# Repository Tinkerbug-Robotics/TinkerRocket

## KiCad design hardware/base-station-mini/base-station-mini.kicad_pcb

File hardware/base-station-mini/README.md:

# base-station-mini

A reduced-feature ground station. **"Mini" means fewer features, not a smaller
board** — the outline is still base-station's 30.27 × 90.50 mm. Nothing here is
trying to shrink; it is trying to do less.

Currently rev **V1**, never fabricated.

## What it drops, and what it gains

Against [`base-station/`](../base-station/):

- **The LoRa radio is on-board.** `U16`, an E220-900MM22S on SPI, replaces the
  UART header that fed an external [`lora-daughterboard/`](../lora-daughterboard/).
  That removes the daughterboard, its connector, and the 5 V `V_LORA` boost that
  supplied it — the module runs straight off +3V3.
- **No external charger sheet.** Dropped from the root, along with the
  `PosADC`/`MidADC` sense lines it fed. `external_charger.kicad_sch` was deleted
  outright on 2026-08-12 rather than left orphaned on disk.
- **No sensor I²C.** `SDA_SENS`/`SCL_SENS` are gone, which is what freed GPIO33
  and GPIO34 for the radio.
- **`+3V3` comes from a fixed-output TPS63021** buck-boost rather than the
  adjustable TPS63020 and its feedback divider. base-station moved to the same
  part at V6.

## The battery thermistor is board-mounted, and that is a compromise

`TH1` feeds the BQ21040's `TS` pin, which gates charging on temperature. It is a
10 kΩ-at-25 °C NTC, B25/85 = 3435 K, ±1 % on both, in an 0603 chip package, on
the component side at the far end of the board from the charger. `R53` (210 kΩ,
`TS` to ground) is TI's TTDM-defeat resistor and is unchanged — with the same
resistance-temperature curve the charger's temperature window does not move.

Until 2026-08-27 `TH1` was a two-pin 2.54 mm land for a **leaded** thermistor of
that same curve, meant to be taped to the 18650 so `TS` read *cell* temperature.
The cell holder leaves no room for a part under the cell, so the sensor moved
onto the board.

**What that costs.** The NTC now reads the ground plane, not the cell, and its
self-heat bias runs one way: a warm board makes the charger believe the pack is
warmer than it is.

- On the hot side that is conservative — charging is inhibited early.
- On the **cold** side it is not. Board self-heat can mask a genuinely cold cell
  and allow a sub-0 °C charge, which is the failure the `TS` pin exists to
  prevent.

Placement mitigates this; it does not remove it. `TH1` sits 25 mm from the
charger — the dominant heat source while charging, dissipating on the order of
1 W as a linear regulator at the ~0.79 A `R52` programs — 27 mm from the
buck-boost and 15 mm from the ESP32-S3. Weighted by dissipation over distance
that is about 37 % less coupling than the old land, which sat 8.6 mm from the
buck-boost and 13.5 mm from the charger. A solid inner ground plane keeps the
board close to isothermal, so what remains is a board-wide offset rather than a
local hot spot.

Everywhere on the board that is further from the heat needs a sensor trace
threaded through the ESP32-S3 fanout or the chip antenna's ground-via fence;
neither is worth it for a few degrees. The route as built is 19 mm on `F.Cu`
with no vias.

**Open at first article:** with the board charging, compare the `TS` node
against a reference probe on the cell at room temperature and near 0 °C, and
confirm the offset is small enough to accept. If it is not, the fix is a wired
probe on a connector, not a different chip.

## The radio pinout is deliberately identical to lora-daughterboard

All eight ESP32↔E220 signals land on the same GPIOs as the fabbed
`lora-daughterboard`, so the `radio_board` firmware pin map applies unchanged:

| net | E220 | GPIO |
|---|---|---|
| `L_SCK` | 15 SCK | 17 |
| `L_CS` | 14 NSS | 18 |
| `L_MOSI` | 13 MOSI | 21 |
| `L_MISO` | 12 MISO | 33 |
| `L_BUSY` | 11 BUSY | 34 |
| `L_RXEN` | 10 RXEN | 35 |
| `L_RST` | 3 NRST | 38 |
| `L_DI01` | 20 DIO1 | 2 |

`L_DI02` is a module-local loop from DIO2 to TXEN, so the SX1262 drives its own
RF switch and costs no GPIO. DIO3 is unconnected. Both match the daughterboard.

## Provenance

The design started as a copy of `base-station` and diverges from there. There is
**no ongoing relationship** between them — nothing is shared, nothing tracks
upstream, and a change to one is not expected to reach the other. Treat anything
still inherited as a first draft to be justified on its own terms.

Two things were deliberately left behind at the fork:

- **`base-station`'s design reviews** (`prefab-review-2026-08-02.md`,
  `power-switch-review-2026-08-02.md`) — records of a review of *that* board.
  Copying them here would assert this board has been reviewed when it has not.
  They remain the best reading on the inherited power architecture; read them
  there.
- **`outputs.kicad_sch`**, an empty sheet in `base-station/` referenced by
  nothing. See the leftovers note in [`../README.md`](../README.md).

## Status

Not fabbed, no tag, no firmware project of its own. Schematic and PCB are in
sync and fully routed — 0 parity issues, 0 unconnected.

Reviewed 2026-08-12: [`prefab-review-2026-08-12.md`](prefab-review-2026-08-12.md).
Four items to close before fab, none of them blockers; the review's *Before fab*
section is the checklist. See also *Sending a board to fab* in
[`../README.md`](../README.md).

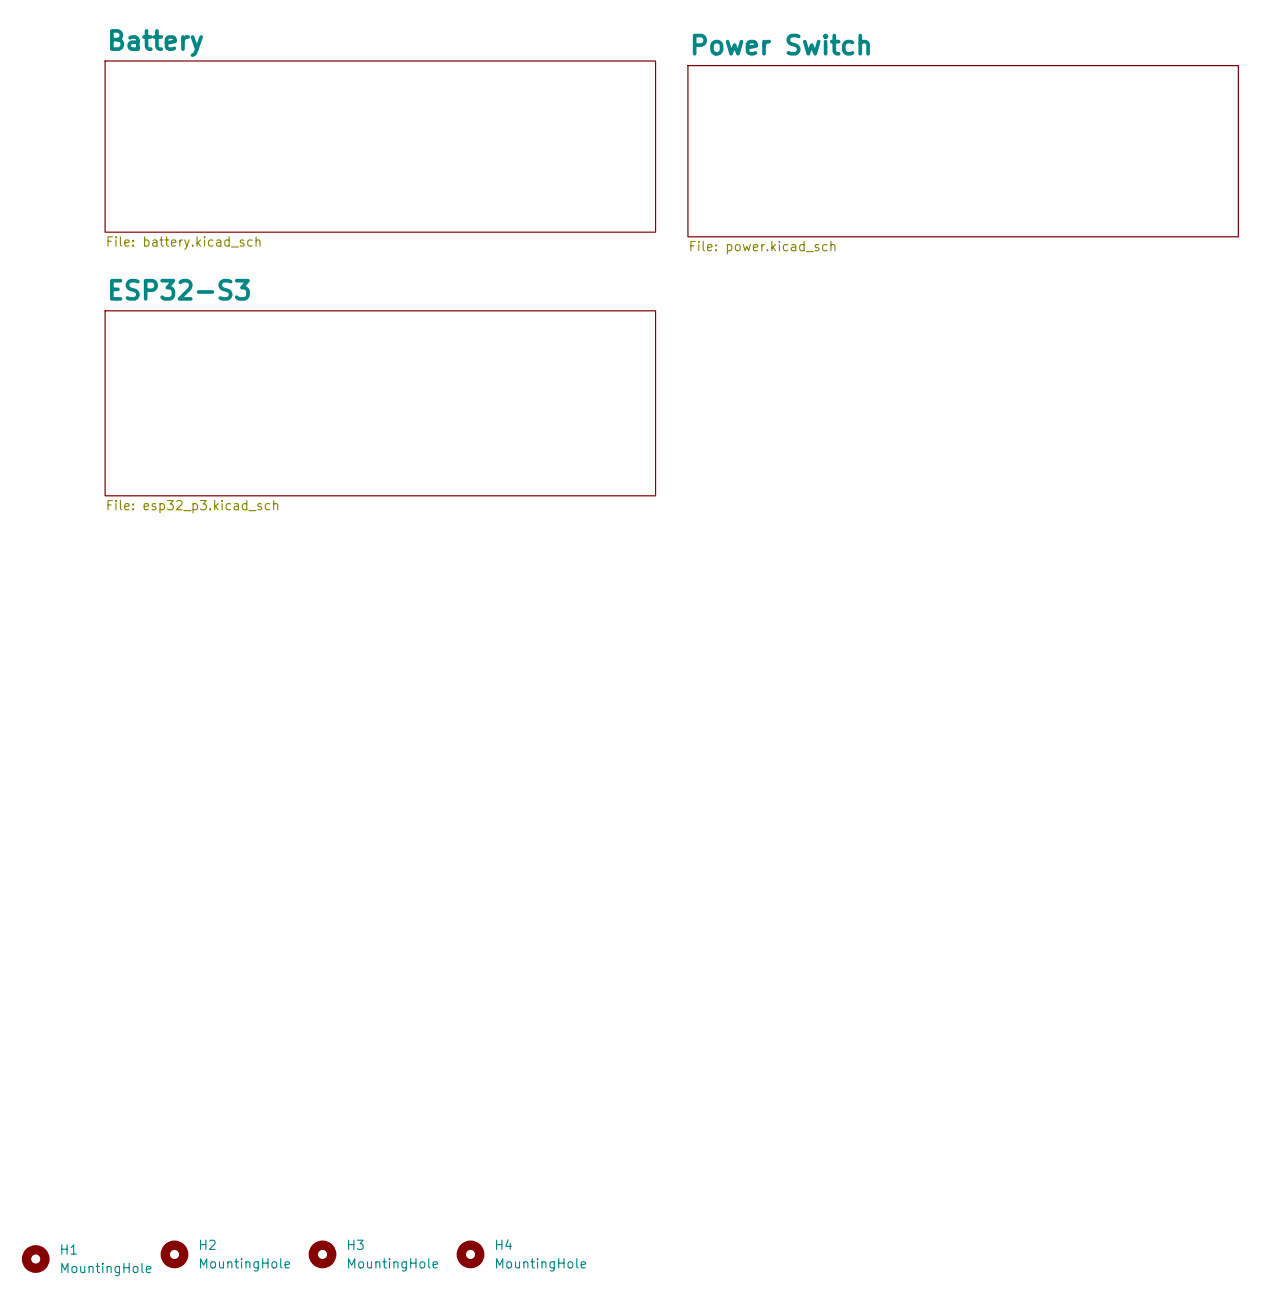
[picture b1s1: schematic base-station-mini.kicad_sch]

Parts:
H1, H2, H3, H4: MountingHole; MountingHole_2.2mm_M2_DIN965_Pad

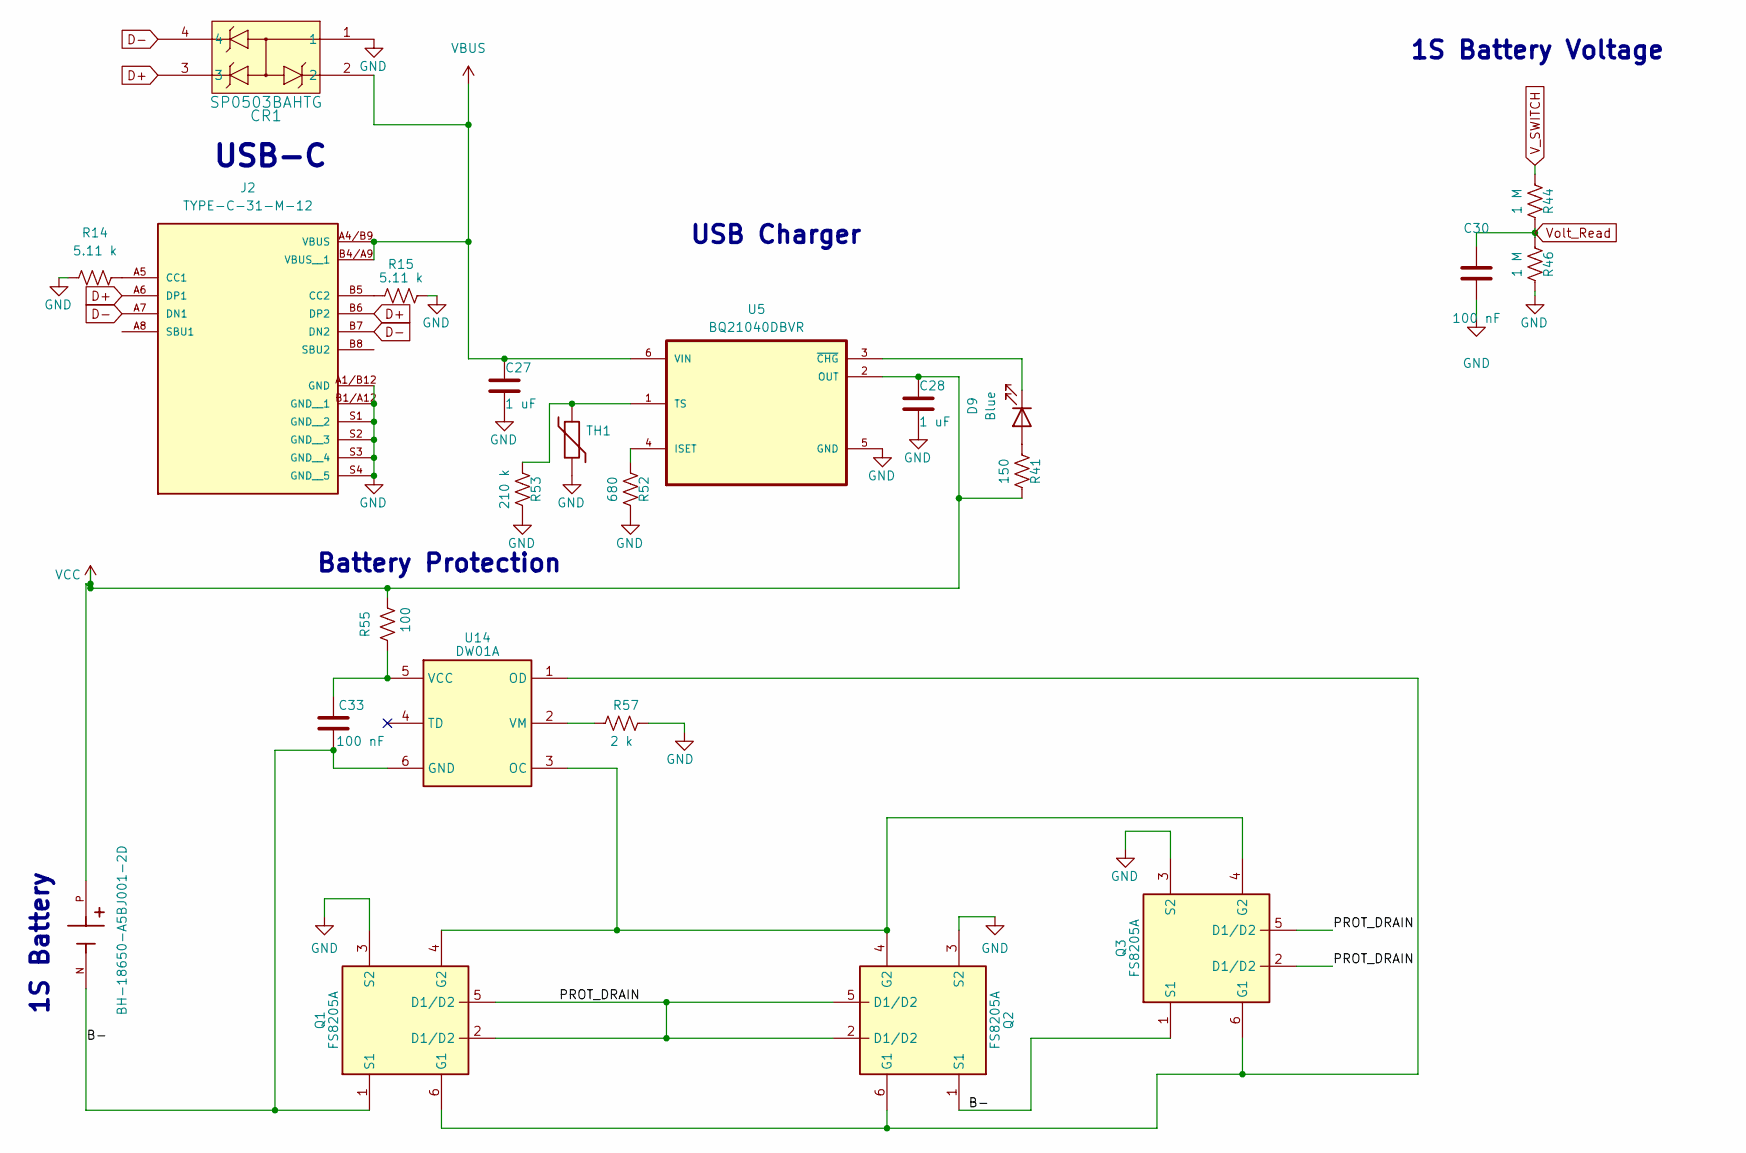
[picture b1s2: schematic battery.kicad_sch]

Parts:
BT2: BH-18650-A5BJ001-2D; BAT_BH-18650-A5BJ001-2D; PARTREV D; LCSC_Part_Number C19184083
C27, C28: 1 uF; C_0402_1005Metric; MPN CL05A105KO5NNNC
C30, C33: 100 nF; C_0402_1005Metric; MPN CL05B104KO5NNNC
CR1: SP0503BAHTG; TVS-SP05_LTF; MPN SP0503BAHTG
D9: Blue; LED_D3.0mm; MPN XL-304UBC
J2: TYPE-C-31-M-12; USB_C_HRO_TYPE-C-31-M-12; MPN TYPE-C-31-M-12
Q1, Q2, Q3: FS8205A; SOT-23-6; MPN FS8205A; LCSC_Part_Number C2830320
R14, R15: 5.11 k; R_0402_1005Metric; MPN RC0402FR-075K11L
R41: 150; R_0402_1005Metric; MPN RC0402FR-07150RL
R44, R46: 1 M; R_0402_1005Metric; MPN RC0402FR-071ML
R52: 680; R_0402_1005Metric; MPN RC0402FR-07680RL
R53: 210 k; R_0402_1005Metric; MPN RC0402FR-07210KL
R55: 100; R_0402_1005Metric; MPN RC0402FR-07100RL
R57: 2 k; R_0402_1005Metric; MPN RC0402FR-072KL
TH1: Thermistor 10k NTC B3435; R_0603_1608Metric; MPN TX06F103F3435ER
U5: BQ21040DBVR; SOT95P280X145-6N; MPN BQ21040DBVR; DigiKey_Part_Number 296-47315-1-ND
U14: DW01A; SOT-23-6; MPN DW01A; LCSC_Part_Number C351410

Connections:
/Battery/B-: BT2.N, C33.2, Q1.1 (S1), Q2.1 (S1), Q3.1 (S1), U14.6 (GND)
/Battery/PROT_DRAIN: Q1.2 (D1/D2), Q1.5 (D1/D2), Q2.2 (D1/D2), Q2.5 (D1/D2), Q3.2 (D1/D2), Q3.5 (D1/D2)
D+: CR1.3, J2.A6 (DP1), J2.B6 (DP2); also elsewhere on the board
D-: CR1.4, J2.A7 (DN1), J2.B7 (DN2); also elsewhere on the board
GND: C27.2, C28.2, C30.2, CR1.1, J2.A1/B12 (GND), J2.B1/A12 (GND__1), J2.S1 (GND__2), J2.S2 (GND__3), J2.S3 (GND__4), J2.S4 (GND__5), Q1.3 (S2), Q2.3 (S2), Q3.3 (S2), R14.1, R15.2, R46.2, R52.2, R53.2, R57.2, TH1.2, U5.5 (GND); also elsewhere on the board
unnamed: D9.2 (A), R41.1
unnamed: D9.1 (K), U5.3 (~CHG)
unnamed: J2.A5 (CC1), R14.2
unnamed: J2.B5 (CC2), R15.1
unnamed: Q1.6 (G1), Q2.6 (G1), Q3.6 (G1), U14.1 (OD)
unnamed: Q1.4 (G2), Q2.4 (G2), Q3.4 (G2), U14.3 (OC)
unnamed: R52.1, U5.4 (ISET)
unnamed: R53.1, TH1.1, U5.1 (TS)
unnamed: C33.1, R55.2, U14.5 (VCC)
unnamed: R57.1, U14.2 (VM)
VBUS: C27.1, CR1.2, J2.A4/B9 (VBUS), J2.B4/A9 (VBUS__1), U5.6 (VIN)
VCC: BT2.P, C28.1, R41.2, R55.1, U5.2 (OUT); also elsewhere on the board
V_SWITCH: R44.1; also elsewhere on the board
Volt_Read: C30.1, R44.2, R46.1; also elsewhere on the board

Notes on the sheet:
1S Battery
1S Battery Voltage
Battery Protection
USB-C
USB Charger

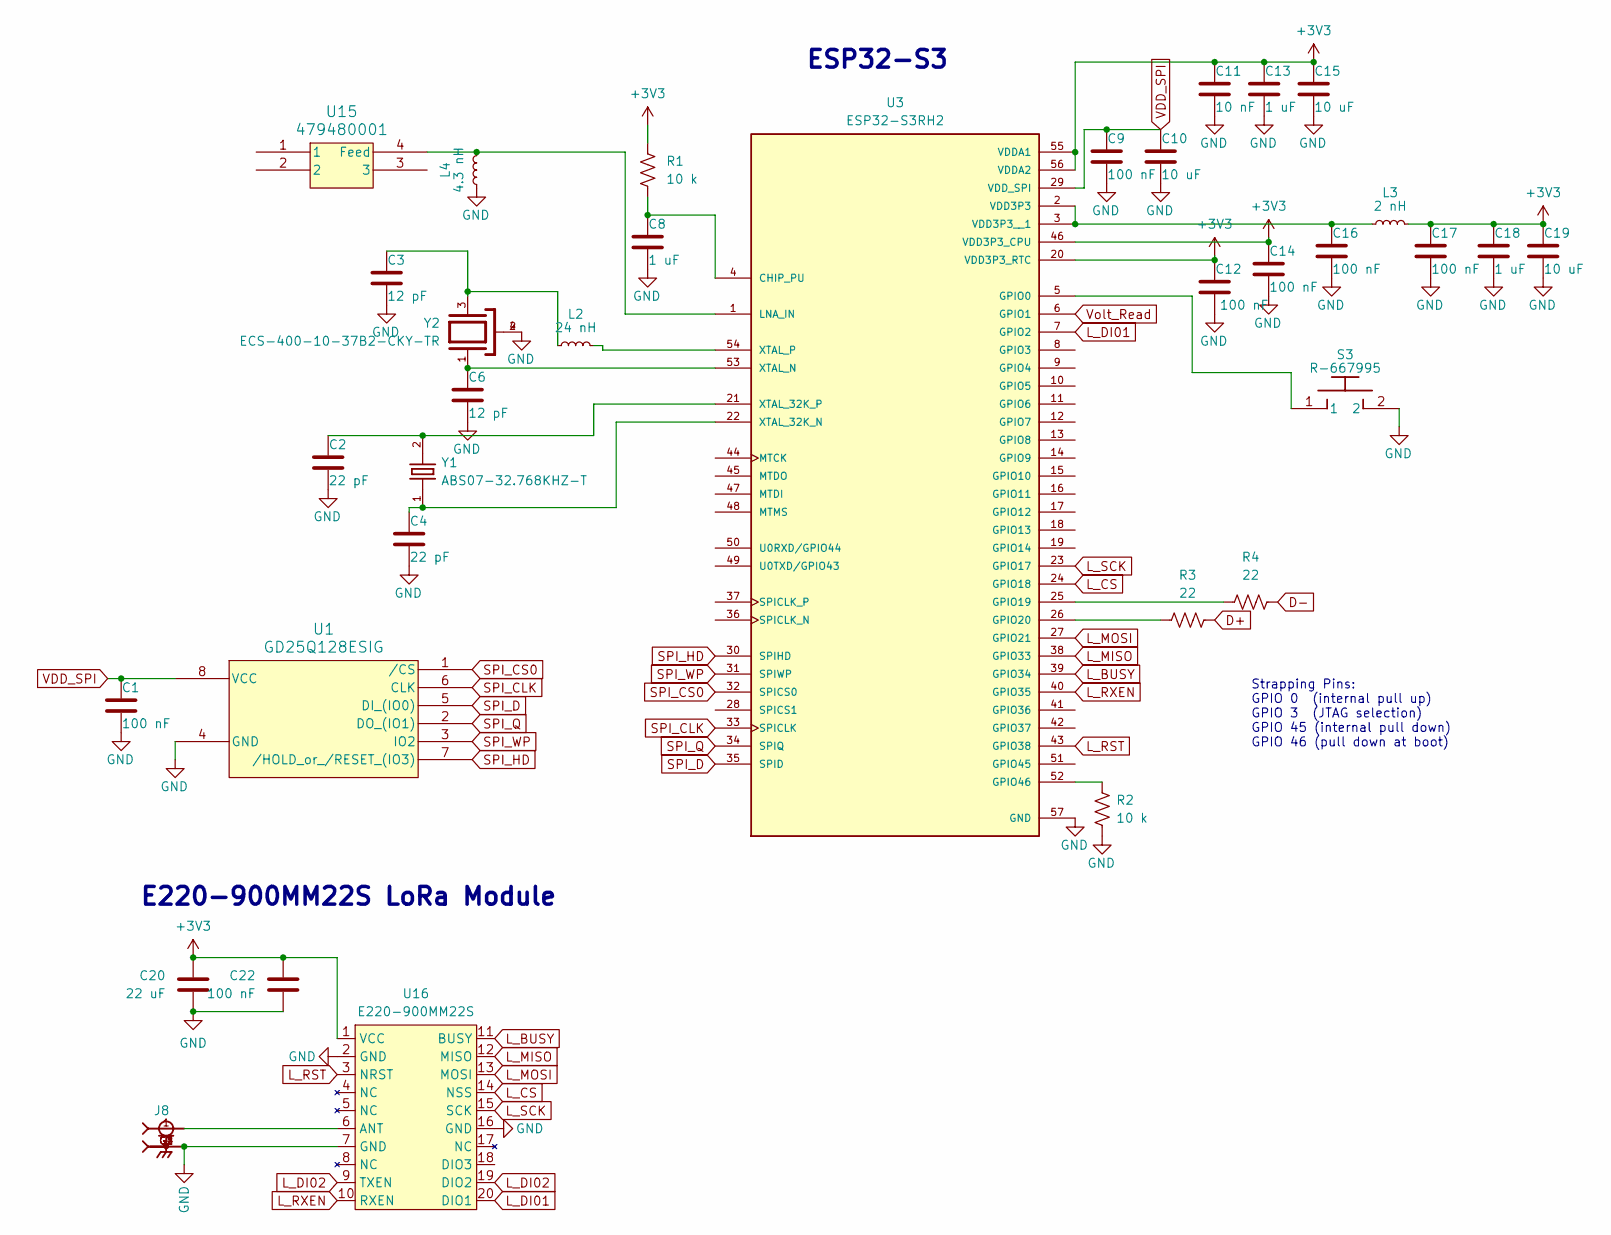
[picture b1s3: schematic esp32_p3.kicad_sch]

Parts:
C1, C9, C12, C14, C16, C17, C22: 100 nF; C_0402_1005Metric; MPN CL05B104KO5NNNC
C2, C4: 22 pF; C_0402_1005Metric; MPN CL05C220JB5NNNC
C3, C6: 12 pF; C_0402_1005Metric; MPN CL05C120JB5NNNC
C8, C13, C18: 1 uF; C_0402_1005Metric; MPN CL05A105KO5NNNC
C10, C15, C19: 10 uF; C_0402_1005Metric; MPN CL05A106MQ5NUNC
C11: 10 nF; C_0402_1005Metric; MPN CL05B103KB5NNNC
C20: 22 uF; C_0805_2012Metric; MPN CL21A226MOQNNNE
J8: CON-SMA-EDGE-S; RFSOLUTIONS_CON-SMA-EDGE-S; PARTREV 1
L2: 24 nH; L_0402_1005Metric; MPN LQW15AN24NH00D
L3: 2 nH; L_0402_1005Metric; MPN LQG15HS2N0S02D
L4: 4.3 nH; L_0402_1005Metric; MPN LQW15AN4N3C00D
R1, R2: 10 k; R_0402_1005Metric; MPN RC0402FR-0710KL
R3, R4: 22; R_0402_1005Metric; MPN RC0402FR-0722RL
S3: R-667995; R-667995_MIT; MPN R-667995
U1: GD25Q128ESIG; SOIC127P790X216-8N; MPN GD25Q128ESIG
U3: ESP32-S3RH2; IC_ESP32-S3; PARTREV v1.2
U15: 479480001; ANT_47948-0001_MOL; MPN 479480001
U16: E220-900MM22S; MPN E220-900MM22S
Y1: ABS07-32.768KHZ-T; XTAL_SC-32S_3215; MPN ABS07-32.768KHZ-T
Y2: ECS-400-10-37B2-CKY-TR; XTAL_ECS-400-10-37B2-CKY-TR; PARTREV 2021

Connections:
+3V3: C11.1, C12.1, C13.1, C14.1, C15.1, C17.1, C18.1, C19.1, C20.2, C22.2, L3.2, R1.1, U3.20 (VDD3P3_RTC), U3.46 (VDD3P3_CPU), U3.55 (VDDA1), U3.56 (VDDA2), U16.1 (VCC); also elsewhere on the board
D+: R3.1; also elsewhere on the board
D-: R4.1; also elsewhere on the board
GND: C1.2, C2.2, C3.2, C4.2, C6.2, C8.2, C9.2, C10.2, C11.2, C12.2, C13.2, C14.2, C15.2, C16.2, C17.2, C18.2, C19.2, C20.1, C22.1, J8.G1, J8.G2, J8.G3, J8.G4, L4.1, R2.2, S3.2, U1.4 (GND), U3.57 (GND), U16.2 (GND), U16.7 (GND), U16.16 (GND), Y2.2, Y2.4; also elsewhere on the board
L_BUSY: U3.39 (GPIO34), U16.11 (BUSY)
L_CS: U3.24 (GPIO18), U16.14 (NSS)
L_DI01: U3.7 (GPIO2), U16.20 (DIO1)
L_DI02: U16.9 (TXEN), U16.19 (DIO2)
L_MISO: U3.38 (GPIO33), U16.12 (MISO)
L_MOSI: U3.27 (GPIO21), U16.13 (MOSI)
L_RST: U3.43 (GPIO38), U16.3 (NRST)
L_RXEN: U3.40 (GPIO35), U16.10 (RXEN)
L_SCK: U3.23 (GPIO17), U16.15 (SCK)
unnamed: C3.1, L2.1, Y2.3
unnamed: C8.1, R1.2, U3.4 (CHIP_PU)
unnamed: S3.1, U3.5 (GPIO0)
unnamed: R4.2, U3.25 (GPIO19)
unnamed: R3.2, U3.26 (GPIO20)
unnamed: R2.1, U3.52 (GPIO46)
unnamed: C16.1, L3.1, U3.2 (VDD3P3), U3.3 (VDD3P3__1)
unnamed: C4.1, U3.22 (XTAL_32K_N), Y1.1
unnamed: C2.1, U3.21 (XTAL_32K_P), Y1.2
unnamed: C6.1, U3.53 (XTAL_N), Y2.1
unnamed: L2.2, U3.54 (XTAL_P)
unnamed: L4.2, U3.1 (LNA_IN), U15.4 (Feed_4)
unnamed: J8.1, U16.6 (ANT)
SPI_CLK: U1.6 (CLK), U3.33 (SPICLK)
SPI_CS0: U1.1 (/CS), U3.32 (SPICS0)
SPI_D: U1.5 (DI_(IO0)), U3.35 (SPID)
SPI_HD: U1.7 (/HOLD_or_/RESET_(IO3)), U3.30 (SPIHD)
SPI_Q: U1.2 (DO_(IO1)), U3.34 (SPIQ)
SPI_WP: U1.3 (IO2), U3.31 (SPIWP)
VDD_SPI: C1.1, C9.1, C10.1, U1.8 (VCC), U3.29 (VDD_SPI)
Volt_Read: U3.6 (GPIO1); also elsewhere on the board

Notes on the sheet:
Strapping Pins: GPIO 0 (internal pull up) GPIO 3 (JTAG selection) GPIO 45 (internal pull down) GPIO 46 (pull down at boot)
ESP32-S3
E220-900MM22S LoRa Module

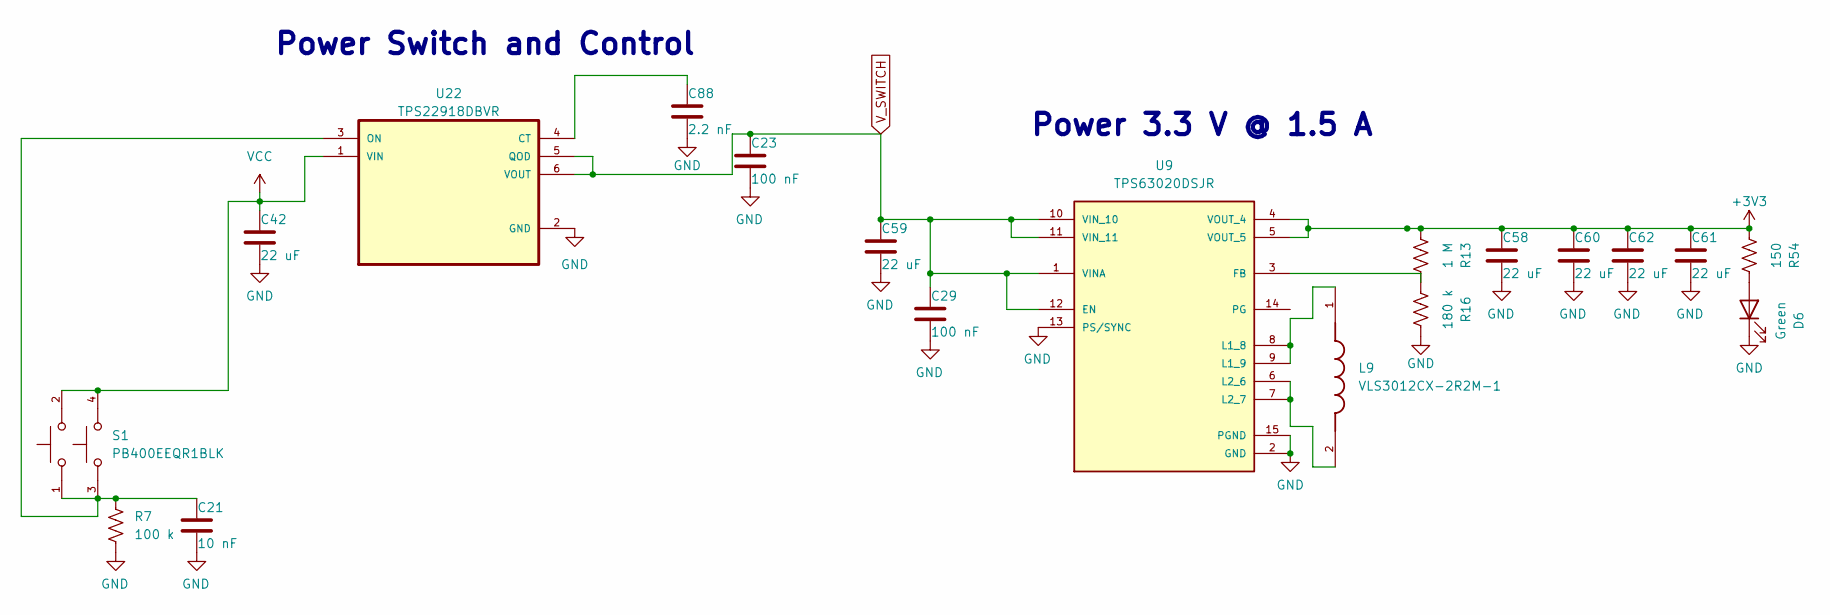
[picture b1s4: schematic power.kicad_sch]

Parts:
C21: 10 nF; C_0402_1005Metric; MPN CL05B103KB5NNNC
C23, C29: 100 nF; C_0402_1005Metric; MPN CL05B104KO5NNNC
C42, C58, C59, C60, C61, C62: 22 uF; C_0805_2012Metric; MPN CL21A226MOQNNNE
C88: 2.2 nF; C_0402_1005Metric; MPN CC0402KRX7R9BB222
D6: Green; LED_D3.0mm; MPN XL-302SYGD
L9: VLS3012CX-2R2M-1; IND_VLS3012CX-2R2M-1; PARTREV N/A
R7: 100 k; R_0402_1005Metric; MPN RC0402FR-07100KL
R13: 1 M; R_0402_1005Metric; MPN RC0402FR-071ML
R16: 180 k; R_0402_1005Metric; MPN RC0402FR-07180KL
R54: 150; R_0402_1005Metric; MPN RC0402FR-07150RL
S1: PB400EEQR1BLK; SW_PB400EEQR1BLK; PARTREV A
U9: TPS63020DSJR; IC_TPS63021DSJR; PARTREV I
U22: TPS22918DBVR; SOT95P280X145-6N; MPN TPS22918DBVR

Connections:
+3V3: C58.1, C60.1, C61.1, C62.1, R13.1, R54.1, U9.4 (VOUT_4), U9.5 (VOUT_5); also elsewhere on the board
GND: C21.2, C23.2, C29.2, C42.2, C58.2, C59.2, C60.2, C61.2, C62.2, C88.2, D6.1 (K), R7.1, R16.2, U9.2 (GND), U9.13 (PS/SYNC), U9.15 (PGND), U22.2 (GND); also elsewhere on the board
unnamed: D6.2 (A), R54.2
unnamed: R13.2, R16.1, U9.3 (FB)
unnamed: L9.1, U9.8 (L1_8), U9.9 (L1_9)
unnamed: L9.2, U9.6 (L2_6), U9.7 (L2_7)
unnamed: C88.1, U22.4 (CT)
unnamed: C21.1, R7.2, S1.1, S1.3, U22.3 (ON)
VCC: C42.1, S1.2, S1.4, U22.1 (VIN); also elsewhere on the board
V_SWITCH: C23.1, C29.1, C59.1, U9.1 (VINA), U9.10 (VIN_10), U9.11 (VIN_11), U9.12 (EN), U22.5 (QOD), U22.6 (VOUT); also elsewhere on the board

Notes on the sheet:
Power Switch and Control
Power 3.3 V @ 1.5 A

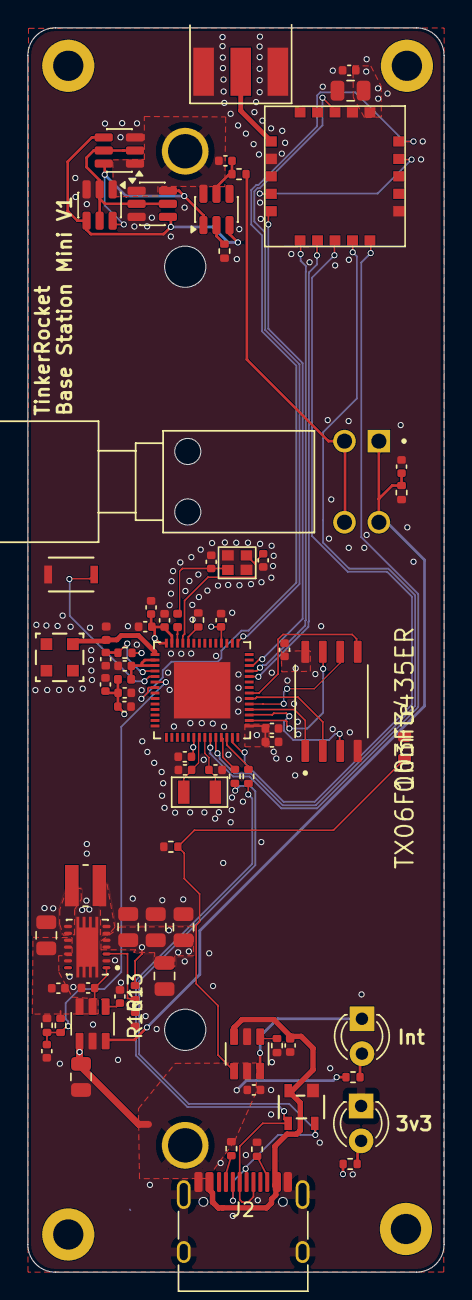
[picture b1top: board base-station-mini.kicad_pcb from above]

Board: 4 copper layers, 30.3 x 90.5 mm, 80 parts (1 on the bottom side), 55 nets.

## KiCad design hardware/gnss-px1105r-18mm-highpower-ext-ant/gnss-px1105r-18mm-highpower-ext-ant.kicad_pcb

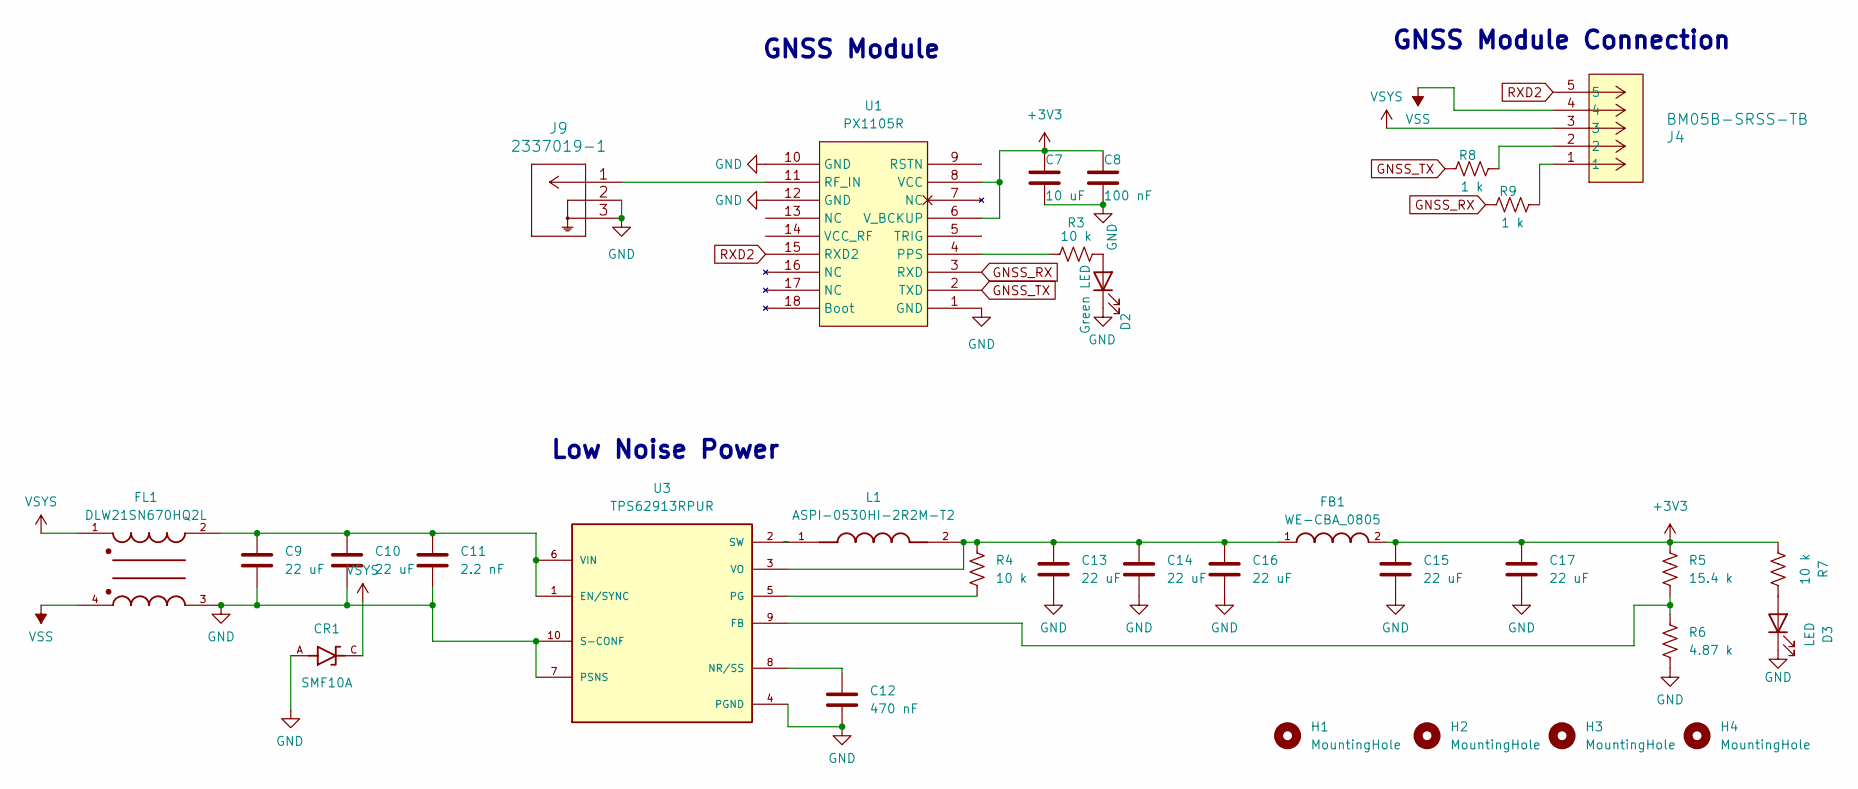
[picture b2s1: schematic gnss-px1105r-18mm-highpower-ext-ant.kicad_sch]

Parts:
C7: 10 uF; C_0805_2012Metric
C8: 100 nF; C_0402_1005Metric
C9, C10, C13, C14, C15, C16, C17: 22 uF; C_0805_2012Metric
C11: 2.2 nF; C_0402_1005Metric
C12: 470 nF; C_0402_1005Metric
CR1: SMF10A; SODFL3617X108N; MPN SMF10A
D2: Green LED; LED_0402_1005Metric
D3: LED; LED_0402_1005Metric
FB1: WE-CBA_0805; WE-CBA_0805_W4.0
FL1: DLW21SN670HQ2L; FIL_DLW21SN670HQ2L
H1, H2, H3, H4: MountingHole; MountingHole_2.2mm_M2_DIN965_Pad
J4: BM05B-SRSS-TB; CONN_BM05B-SRSS-TB_JST
J9: 2337019-1
L1: ASPI-0530HI-2R2M-T2; IND_ASPI-0530HI-2R2M-T2; PARTREV B; DigiKey_Part_Number 535-ASPI-0530HI-2R2M-T2CT-ND
R3, R4, R7: 10 k; R_0402_1005Metric
R5: 15.4 k; R_0402_1005Metric
R6: 4.87 k; R_0402_1005Metric
R8, R9: 1 k; R_0402_1005Metric
U1: PX1105R
U3: TPS62913RPUR; IC_TPS62913RPUR; PARTREV B; DigiKey_Part_Number 296-TPS62913RPURCT-ND

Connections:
+3V3: C7.1, C8.1, C15.1, C17.1, FB1.2, R5.2, R7.1, U1.6 (V_BCKUP), U1.8 (VCC)
GND: C7.2, C8.2, C9.2, C10.2, C11.2, C12.2, C13.2, C14.2, C15.2, C16.2, C17.2, CR1.A, D2.1 (K), D3.1 (K), FL1.3, J9.2, J9.3, R6.1, U1.1 (GND), U1.10 (GND), U1.12 (GND), U3.4 (PGND), U3.7 (PSNS), U3.10 (S-CONF)
GNSS_RX: R9.1, U1.3 (RXD)
GNSS_TX: R8.1, U1.2 (TXD)
unnamed: D2.2 (A), R3.2
unnamed: D3.2 (A), R7.2
unnamed: J4.1, R9.2
unnamed: J4.2, R8.2
unnamed: R3.1, U1.4 (PPS)
unnamed: J9.1, U1.11 (RF_IN)
unnamed: C9.1, C10.1, C11.1, FL1.2, U3.1 (EN/SYNC), U3.6 (VIN)
unnamed: R5.1, R6.2, U3.9 (FB)
unnamed: C12.1, U3.8 (NR/SS)
unnamed: R4.1, U3.5 (PG)
unnamed: L1.1, U3.2 (SW)
unnamed: C13.1, C14.1, C16.1, FB1.1, L1.2, R4.2, U3.3 (VO)
RXD2: J4.5, U1.15 (RXD2)
VSS: FL1.4, J4.4
VSYS: CR1.C, FL1.1, J4.3

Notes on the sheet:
Low Noise Power
GNSS Module
GNSS Module Connection

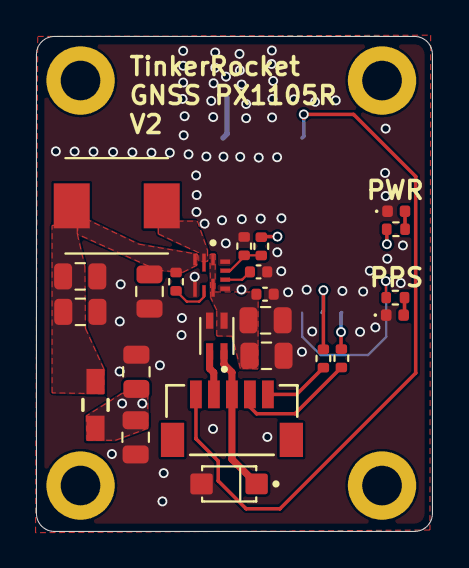
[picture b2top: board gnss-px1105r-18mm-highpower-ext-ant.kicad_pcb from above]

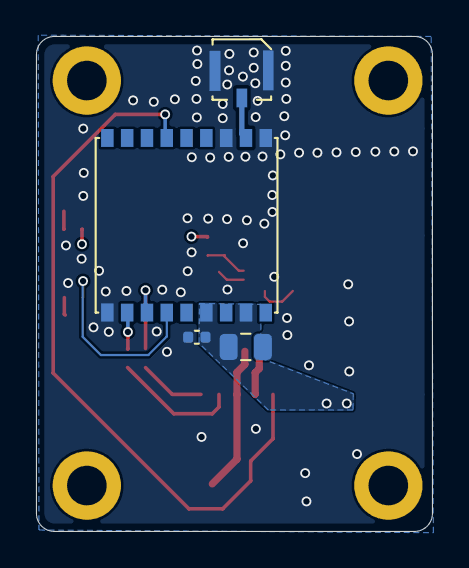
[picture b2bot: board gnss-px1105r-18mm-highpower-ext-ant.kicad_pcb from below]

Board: 4 copper layers, 22.0 x 27.5 mm, 32 parts (4 on the bottom side), 19 nets.

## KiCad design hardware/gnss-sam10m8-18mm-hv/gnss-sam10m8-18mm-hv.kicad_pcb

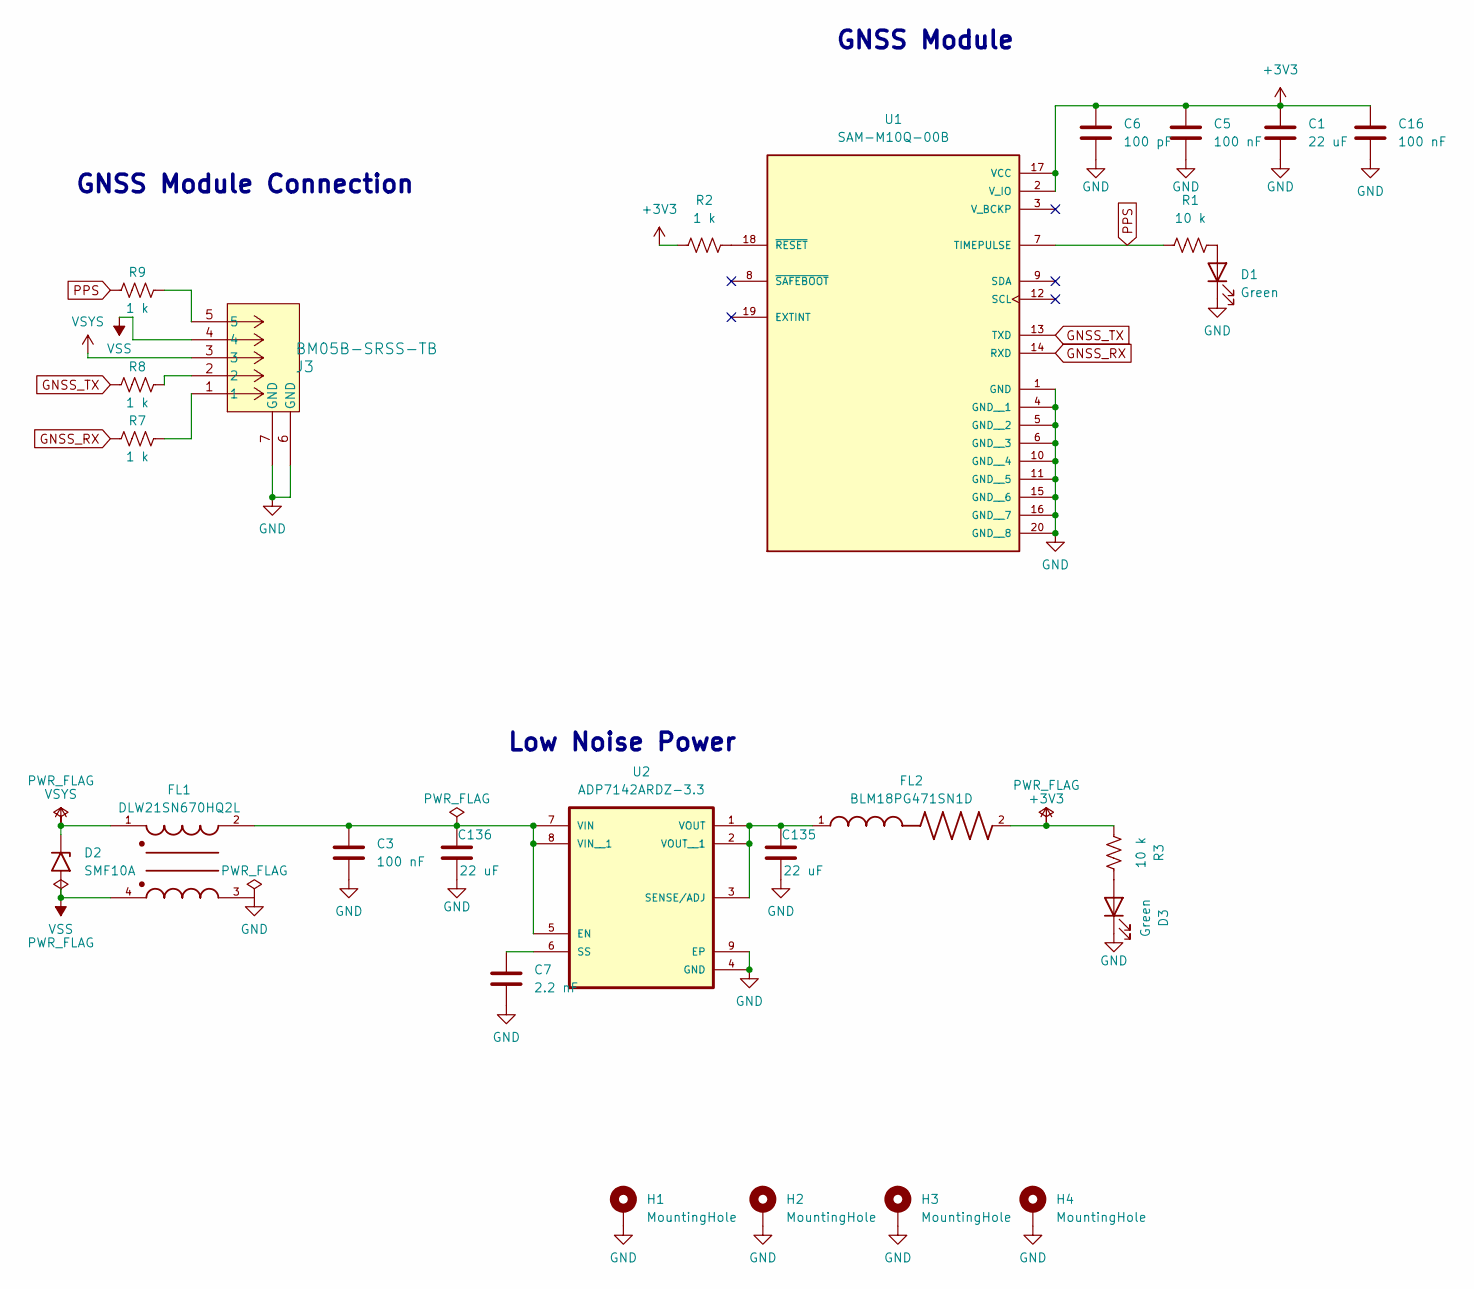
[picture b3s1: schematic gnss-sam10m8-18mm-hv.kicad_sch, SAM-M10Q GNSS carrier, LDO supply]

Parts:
C1, C135, C136: 22 uF; C_0805_2012Metric; MPN CL21A226MOQNNNE
C3, C5, C16: 100 nF; C_0402_1005Metric; MPN CL05B104KO5NNNC
C6: 100 pF; C_0402_1005Metric; MPN CL05C101JB5NNNC
C7: 2.2 nF; C_0402_1005Metric; MPN CC0402KRX7R9BB222
D1, D3: Green; LED_0402_1005Metric; MPN XL-1005UGC
D2: SMF10A; D_SMF; MPN SMF10A
FL1: DLW21SN670HQ2L; FIL_DLW21SN670HQ2L; MPN DLW21SN670HQ2L
FL2: BLM18PG471SN1D; BEADC1608X95N; MPN BLM18PG471SN1D
H1, H2, H3, H4: MountingHole; MountingHole_2.2mm_M2_DIN965_Pad
J3: BM05B-SRSS-TB; CONN_BM05B-SRSS-TB_JST; MPN BM05B-SRSS-TB
R1, R3: 10 k; R_0402_1005Metric; MPN RC0402FR-0710KL
R2, R7, R8, R9: 1 k; R_0402_1005Metric; MPN RC0402FR-071KL
U1: SAM-M10Q-00B; XCVR_SAM-M10Q-00B; MPN SAM-M10Q-00B
U2: ADP7142ARDZ-3.3; SOIC127P600X175-9N; MPN ADP7142ARDZ-3.3

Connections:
+3V3: C1.1, C5.1, C6.1, C16.1, FL2.2, R2.1, R3.1, U1.2 (V_IO), U1.17 (VCC)
GND: C1.2, C3.2, C5.2, C6.2, C7.2, C16.2, C135.2, C136.2, D1.1 (K), D3.1 (K), FL1.3, H1.1 (1_1), H2.1 (1_1), H3.1 (1_1), H4.1 (1_1), J3.6 (GND), J3.7 (GND), U1.1 (GND), U1.4 (GND__1), U1.5 (GND__2), U1.6 (GND__3), U1.10 (GND__4), U1.11 (GND__5), U1.15 (GND__6), U1.16 (GND__7), U1.20 (GND__8), U2.4 (GND), U2.9 (EP)
GNSS_RX: R7.1, U1.14 (RXD)
GNSS_TX: R8.1, U1.13 (TXD)
unnamed: D1.2 (A), R1.2
unnamed: D3.2 (A), R3.2
unnamed: J3.1, R7.2
unnamed: J3.2, R8.2
unnamed: J3.5, R9.2
unnamed: R2.2, U1.18 (~RESET)
unnamed: C3.1, C136.1, FL1.2, U2.5 (EN), U2.7 (VIN), U2.8 (VIN__1)
unnamed: C135.1, FL2.1, U2.1 (VOUT), U2.2 (VOUT__1), U2.3 (SENSE/ADJ)
unnamed: C7.1, U2.6 (SS)
PPS: R1.1, R9.1, U1.7 (TIMEPULSE)
VSS: D2.2 (A2), FL1.4, J3.4
VSYS: D2.1 (A1), FL1.1, J3.3

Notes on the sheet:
GNSS Module
Low Noise Power
GNSS Module Connection

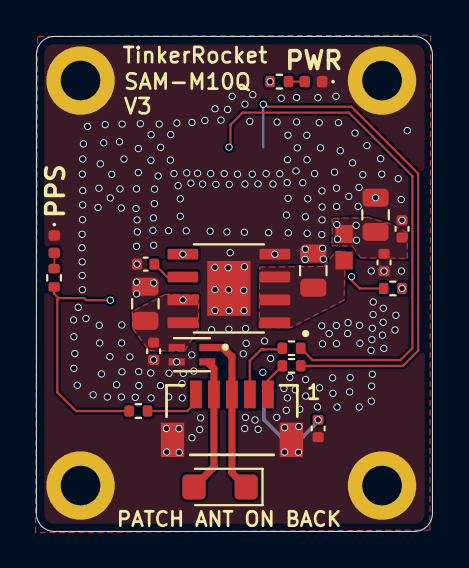
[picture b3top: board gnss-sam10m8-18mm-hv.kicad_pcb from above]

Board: 6 copper layers, 22.0 x 27.5 mm, 26 parts (1 on the bottom side), 16 nets.

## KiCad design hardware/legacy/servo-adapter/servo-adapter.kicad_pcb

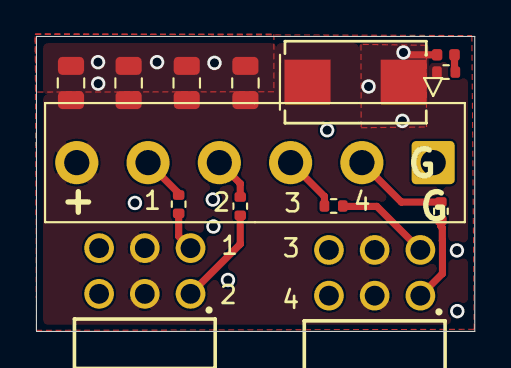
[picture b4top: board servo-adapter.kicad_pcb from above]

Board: 4 copper layers, 24.4 x 16.4 mm, 14 parts (0 on the bottom side), 11 nets.

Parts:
C1, C2, C3, C4: 22 uF; C_0805_2012Metric
C5: TCJE337M016R0050; CAPMP7.6X4.3_3.1N_KEM
D1: White; LED_0402_1005Metric
J1: Conn_01x06_Pin; TE_826576-6_1x06_P3.96mm_Vertical
J2, J3: 6130XX21021_61300621021; 61300621021
R1, R2, R3, R4: 330; R_0402_1005Metric
R13: 10 k; R_0402_1005Metric

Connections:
GND: C1.2, C2.2, C3.2, C4.2, C5.2, D1.1 (K), J1.1, J2.5, J2.6, J3.5, J3.6
LiPoPos: C1.1, C2.1, C3.1, C4.1, C5.1, J1.6, J2.3, J2.4, J3.3, J3.4, R13.1
unnamed: D1.2 (A), R13.2
Servo1: J2.2, R1.2
Servo1_In: J1.5, R1.1
Servo2: J2.1, R2.2
Servo2_In: J1.4, R2.1
Servo3: J3.2, R3.2
Servo3_In: J1.3, R3.1
Servo4: J3.1, R4.2
Servo4_In: J1.2, R4.1
